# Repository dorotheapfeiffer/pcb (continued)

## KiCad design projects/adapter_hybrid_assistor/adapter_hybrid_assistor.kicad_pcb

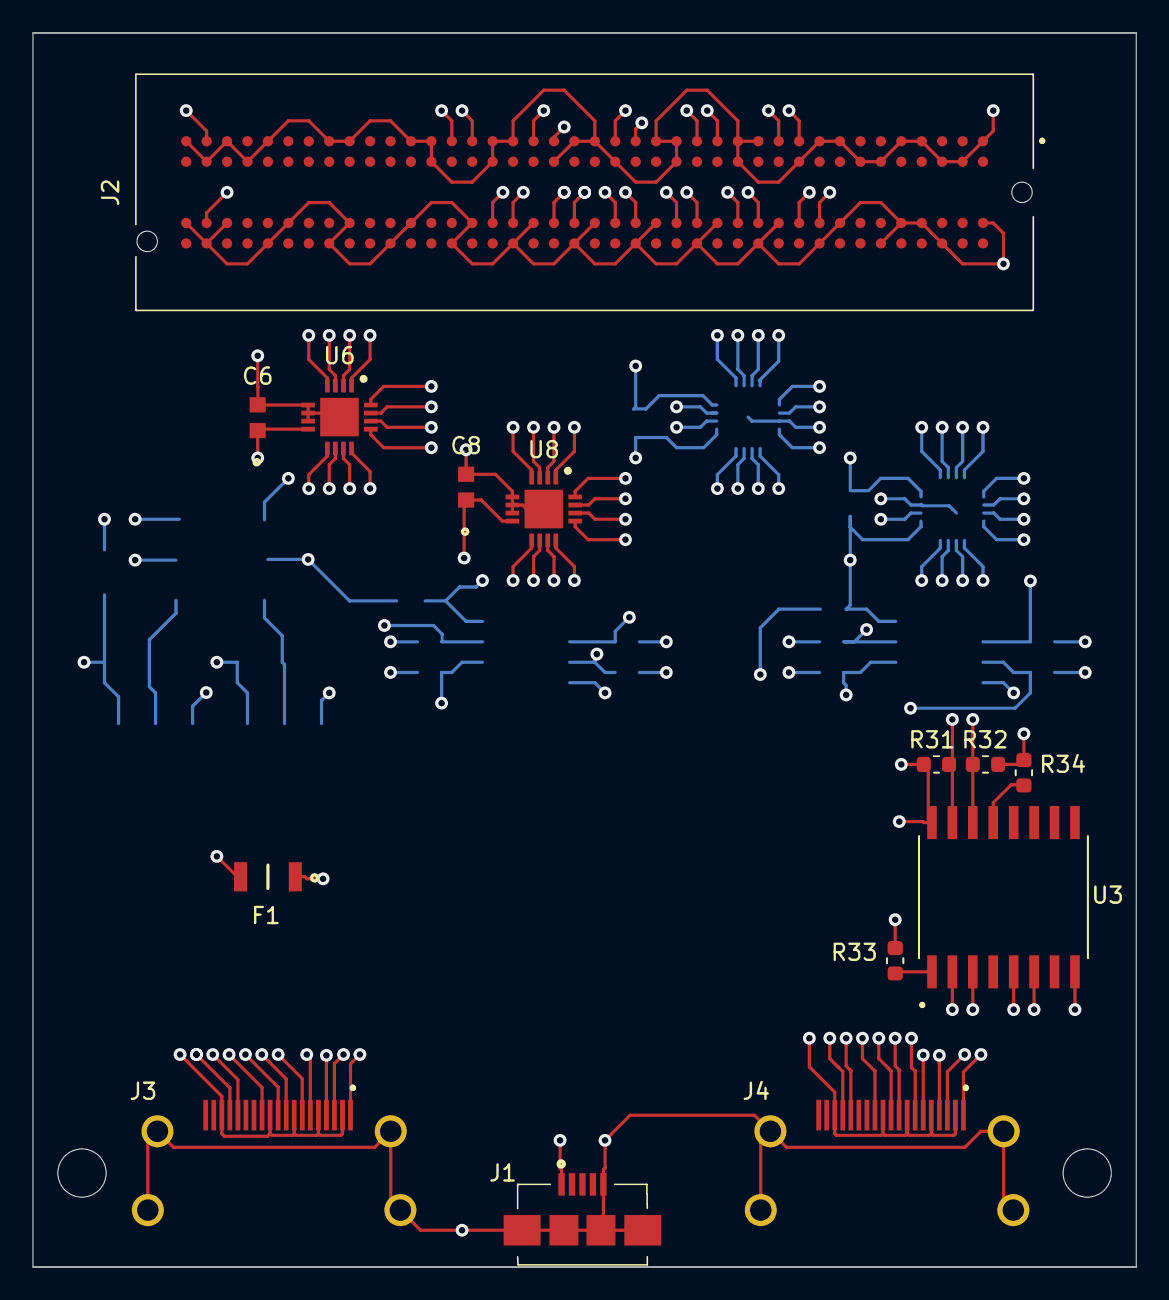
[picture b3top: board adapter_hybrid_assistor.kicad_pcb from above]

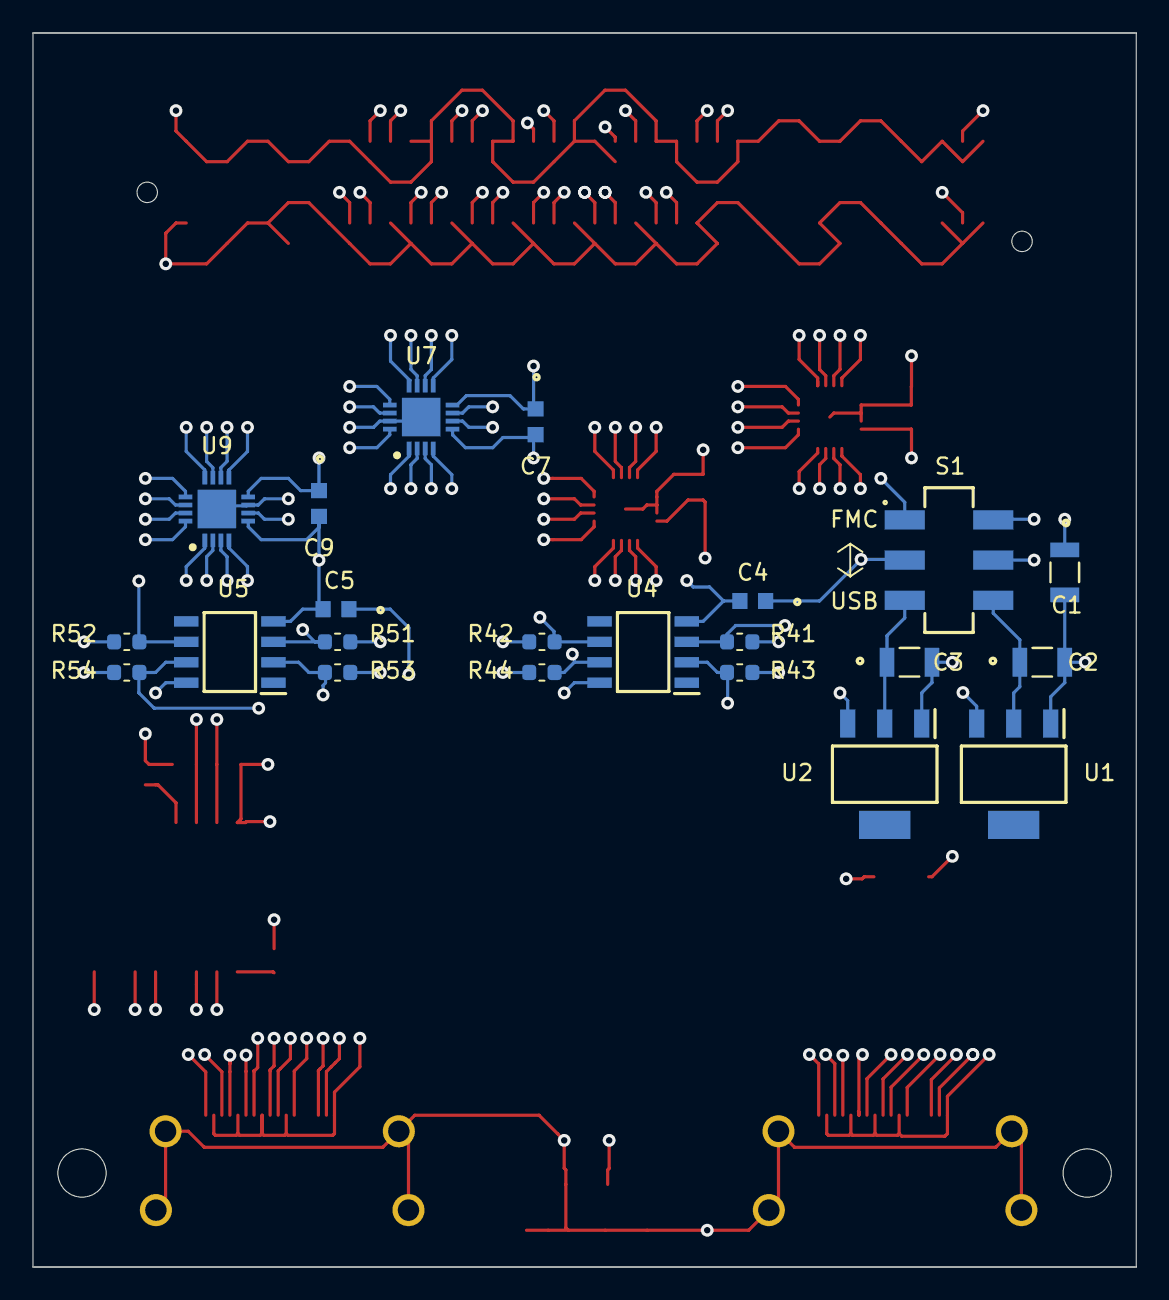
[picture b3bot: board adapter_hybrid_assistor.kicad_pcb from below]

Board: 6 copper layers, 68.6 x 76.7 mm, 36 parts (22 on the bottom side), 55 nets.

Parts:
C1, C2, C3: 10uF; C1206C106K4RACTU
C4, C5, C6, C7, C8, C9: 100nF; C0603C104K4RACTU
F1: 1206L050YR; FUSC3216X75N
J1: 10104110-0001LF; 101041100001LF
J2: ASP-134604-01; ASP13460401
J3, J4: 10029449-001RLF; 10029449001RLF
R31, R32, R33, R41, R42, R51, R52: 4.7k; R_0603_1608Metric
R34: 100k; R_0603_1608Metric
R43, R44, R53, R54: 330; R_0603_1608Metric
S1: JS202011SCQN
U1: TLV1117-33; TLV1117-33IDCYG3
U2: TLV1117-25; TLV1117-25CDCYRG3
U3: PCA9534DW; SOIC127P1030X265-16N
U4, U5: P82B715DR
U6, U7, U8, U9: DS25CP102TSQ; QFN50P400X400X80-17N

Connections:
2.5V: C4.1, C5.1, R43.1, R44.1, R53.1, R54.1, S1.2
2.5V_Supply: C3.1, S1.3, U2.2
2.5V_VADJ_FMC: J2.G39, S1.1
3.3V: C6.1, C7.1, C8.1, C9.1, R31.1, R32.1, R33.1, R34.1, R41.1, R42.1, R51.1, R52.1, S1.5, U3.16, U4.8, U5.8, U6.8, U6.13, U6.14, U6.16, U7.8, U7.13, U7.14, U7.16, U8.8, U8.13, U8.14, U8.16, U9.8, U9.13, U9.14, U9.16
3.3V_FMC: J2.C39, S1.4
3.3V_Supply: C2.1, S1.6, U1.2
/5.0V: C1.1, F1.2, U1.3, U2.3
/5.0V_USB: F1.1, J1.1
/A0: R33.2, U3.1
/D_OUT_M1_1N: J2.C11, U7.11
/D_OUT_M1_1P: J2.C10, U7.12
/D_OUT_M2_1N: J2.C15, U7.9
/D_OUT_M2_1P: J2.C14, U7.10
/~INT: R34.2, U3.13
BCLK_1N: J2.C23, U6.4
BCLK_1P: J2.C22, U6.3
BCLK_2N: J2.G19, U8.4
BCLK_2P: J2.G18, U8.3
D_OUT_M1_2N: J2.G10, U9.11
D_OUT_M1_2P: J2.G9, U9.12
D_OUT_M2_2N: J2.G13, U9.9
D_OUT_M2_2P: J2.G12, U9.10
EQ: U3.6, U7.6, U9.6
GNDREF: C1.2, C2.2, C3.2, C4.2, C5.2, C6.2, C7.2, C8.2, C9.2, J1.5, J1.MP1, J1.MP2, J1.MP3, J1.MP4, J2.C1, J2.C4, J2.C5, J2.C8, J2.C9, J2.C12, J2.C13, J2.C16, J2.C17, J2.C20, J2.C21, J2.C24, J2.C25, J2.C28, J2.C29, J2.C32, J2.C33, J2.C36, J2.C38, J2.C40, J2.D2, J2.D3, J2.D6, J2.D7, J2.D10, J2.D13, J2.D16, J2.D19, J2.D22, J2.D25, J2.D28, J2.D37, J2.D39, J2.G1, J2.G4, J2.G5, J2.G8, J2.G11, J2.G14, J2.G17, J2.G20, J2.G23, J2.G26, J2.G29, J2.G32, J2.G35, J2.G38, J2.G40, J2.H3, J2.H6, J2.H9, J2.H12, J2.H15, J2.H18, J2.H21, J2.H24, J2.H27, J2.H30, J2.H33, J2.H36, J2.H39, J3.2, J3.5, J3.8, J3.11, J3.17, J3.MH1, J3.MH2, J3.MH3, J3.MH4, J4.2, J4.5, J4.8, J4.11, J4.17, J4.MH1, J4.MH2, J4.MH3, J4.MH4, U1.1, U2.1, U3.2, U3.3, U3.8, U4.4, U5.4, U6.5, U6.6, U6.7, U6.17, U7.5, U7.7, U7.15, U7.17, U8.5, U8.6, U8.7, U8.17, U9.5, U9.7, U9.15, U9.17
H_BCLK_1N: J3.12, U6.9
H_BCLK_1P: J3.10, U6.10
H_BCLK_2N: J4.12, U8.9
H_BCLK_2P: J4.10, U8.10
H_DOUT_M1_1N: J3.3, U7.2
H_DOUT_M1_1P: J3.1, U7.1
H_DOUT_M1_2N: J4.3, U9.2
H_DOUT_M1_2P: J4.1, U9.1
H_DOUT_M2_1N: J3.6, U7.4
H_DOUT_M2_1P: J3.4, U7.3
H_DOUT_M2_2N: J4.6, U9.4
H_DOUT_M2_2P: J4.4, U9.3
H_SCL0B_1: J3.15, R44.2, U4.7
H_SCL0B_2: J4.15, R54.2, U5.7
H_SDA0B_1: J3.16, R43.2, U4.2
H_SDA0B_2: J4.16, R53.2, U5.2
H_TRG_1N: J3.9, U6.11
H_TRG_1P: J3.7, U6.12
H_TRG_2N: J4.9, U8.11
H_TRG_2P: J4.7, U8.12
PE: U3.5, U6.15, U8.15
SCL0B_1: J2.C26, R42.2, U4.6
SCL0B_2: J2.G21, R52.2, U5.6
SCL1B: J2.G24, R32.2, U3.14
SDA0B_1: J2.C27, R41.2, U4.3
SDA0B_2: J2.G22, R51.2, U5.3
SDA1B: J2.G25, R31.2, U3.15
TRG_1N: J2.C19, U6.2
TRG_1P: J2.C18, U6.1
TRG_2N: J2.G16, U8.2
TRG_2P: J2.G15, U8.1

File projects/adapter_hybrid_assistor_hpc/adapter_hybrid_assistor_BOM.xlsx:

Id | Designator | Designation | Package | Quantity | Value | Place_YES/NO | Provided_by_customer_YES/NO | Supplier | Supplier ref | Manufacturer | Montage
2 | J1 | ASP13460401 |  | 1 |  | YES | NO | Mouser | 200-ASP-134604-01 | Samtec | Solder Balls
6 | U7,U6,U9,U8 | DS25CP102TSQ | WQFN-16 | 4 |  | YES | NO | Mouser | 926-DS25CP102TSQNOPB | Texas Instruments | SMD/SMT
7 | U5,U4 | P82B715DR | SOIC-8 | 2 |  | YES | NO | Mouser | 595-P82B715DR | Texas Instruments | SMD/SMT
11 | J2,J3 | 10029449001RLF |  | 2 |  | YES | NO | Mouser | 649-10029449-001RLF | Amphenol FCI | SMD/SMT
12 | R41,R42,R51,R52 | ERA-3ARB472V | 0603 (1608 metric) | 4 | 4.7k | YES | NO | Mouser | 667-ERA-3ARB472V | Panasonic | SMD/SMT
14 | R43,R44,R53,R54 | ERA-3AED331V | 0603 (1608 metric) | 4 | 330 | YES | NO | Mouser | 667-ERA-3AED331V | Panasonic | SMD/SMT
15 | C4,C5,C6,C7,C8,C9 | C0603C104K4RACTU | 0603 (1608 metric) | 6 | 100nF | YES | NO | Mouser | 80-C0603C104K4R | KEMET | SMD/SMT
 |  |  |  | 23

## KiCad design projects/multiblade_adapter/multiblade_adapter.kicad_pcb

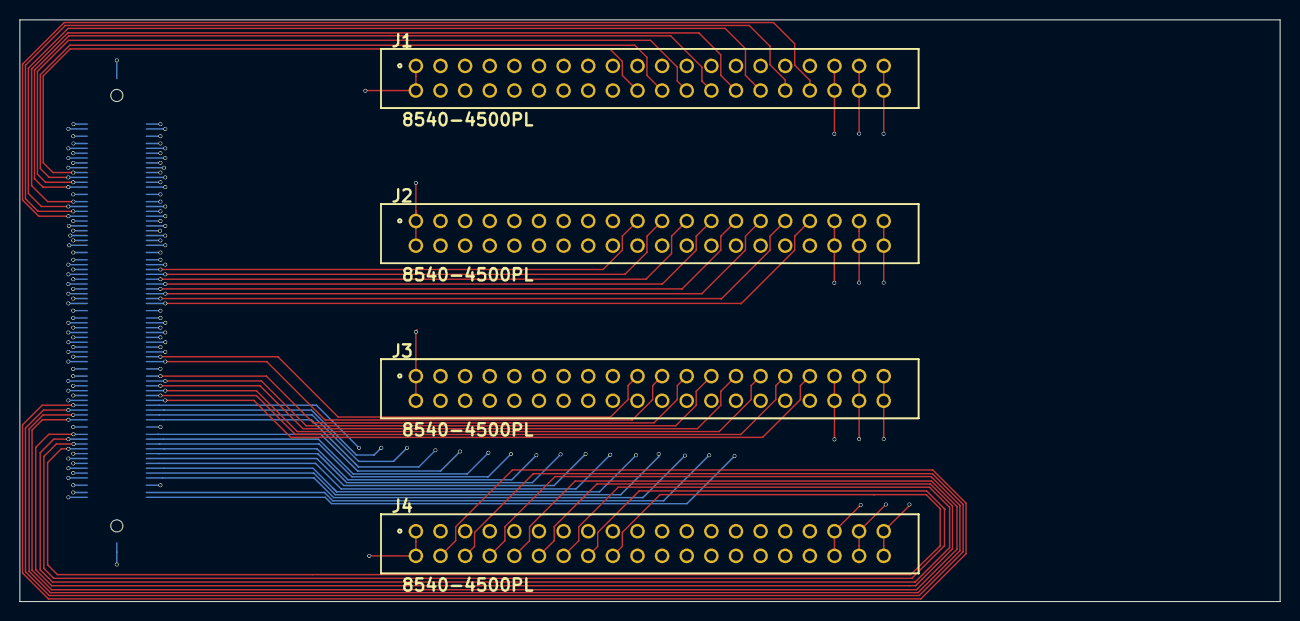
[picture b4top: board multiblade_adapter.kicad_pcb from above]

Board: 6 copper layers, 130.0 x 60.0 mm, 5 parts (1 on the bottom side), 129 nets.

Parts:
J1, J2, J3, J4: 8540-4500PL; 3M-8540-4500PL
J5: FX10A-140S14-SV

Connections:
GND: J1.1, J1.2, J1.35, J1.36, J1.37, J1.38, J1.39, J1.40, J2.1, J2.2, J2.35, J2.36, J2.37, J2.38, J2.39, J2.40, J3.1, J3.2, J3.35, J3.36, J3.37, J3.38, J3.39, J3.40, J4.1, J4.2, J4.35, J4.36, J4.37, J4.38, J4.39, J4.40, J5.141, J5.142, J5.143, J5.144, J5.145, J5.146, J5.147, J5.148, J5.149, J5.150, J5.151, J5.152, J5.153, J5.154, J5.155, J5.156
ch1_1: J1.3, J5.8
ch1_2: J2.3, J5.40
ch1_3: J3.3, J5.72
ch1_4: J4.3, J5.104
ch2_1: J1.4, J5.7
ch2_2: J2.4, J5.39
ch2_3: J3.4, J5.71
ch2_4: J4.4, J5.103
ch3_1: J1.5, J5.10
ch3_2: J2.5, J5.42
ch3_3: J3.5, J5.74
ch3_4: J4.5, J5.106
ch4_1: J1.6, J5.9
ch4_2: J2.6, J5.41
ch4_3: J3.6, J5.73
ch4_4: J4.6, J5.105
ch5_1: J1.7, J5.12
ch5_2: J2.7, J5.44
ch5_3: J3.7, J5.76
ch5_4: J4.7, J5.108
ch6_1: J1.8, J5.11
ch6_2: J2.8, J5.43
ch6_3: J3.8, J5.75
ch6_4: J4.8, J5.107
ch7_1: J1.9, J5.14
ch7_2: J2.9, J5.46
ch7_3: J3.9, J5.78
ch7_4: J4.9, J5.110
ch8_1: J1.10, J5.13
ch8_2: J2.10, J5.45
ch8_3: J3.10, J5.77
ch8_4: J4.10, J5.109
ch9_1: J1.11, J5.16
ch9_2: J2.11, J5.48
ch9_3: J3.11, J5.80
ch9_4: J4.11, J5.112
ch10_1: J1.12, J5.15
ch10_2: J2.12, J5.47
ch10_3: J3.12, J5.79
ch10_4: J4.12, J5.111
ch11_1: J1.13, J5.18
ch11_2: J2.13, J5.50
ch11_3: J3.13, J5.82
ch11_4: J4.13, J5.114
ch12_1: J1.14, J5.17
ch12_2: J2.14, J5.49
ch12_3: J3.14, J5.81
ch12_4: J4.14, J5.113
ch13_1: J1.15, J5.20
ch13_2: J2.15, J5.52
ch13_3: J3.15, J5.84
ch13_4: J4.15, J5.116
ch14_1: J1.16, J5.19
ch14_2: J2.16, J5.51
ch14_3: J3.16, J5.83
ch14_4: J4.16, J5.115
ch15_1: J1.17, J5.22
ch15_2: J2.17, J5.54
ch15_3: J3.17, J5.86
ch15_4: J4.17, J5.118
ch16_1: J1.18, J5.21
ch16_2: J2.18, J5.53
ch16_3: J3.18, J5.85
ch16_4: J4.18, J5.117
ch17_1: J1.19, J5.24
ch17_2: J2.19, J5.56
ch17_3: J3.19, J5.88
ch17_4: J4.19, J5.120
ch18_1: J1.20, J5.23
ch18_2: J2.20, J5.55
ch18_3: J3.20, J5.87
ch18_4: J4.20, J5.119
ch19_1: J1.21, J5.26
ch19_2: J2.21, J5.58
ch19_3: J3.21, J5.90
ch19_4: J4.21, J5.122
ch20_1: J1.22, J5.25
ch20_2: J2.22, J5.57
ch20_3: J3.22, J5.89
ch20_4: J4.22, J5.121
ch21_1: J1.23, J5.28
ch21_2: J2.23, J5.60
ch21_3: J3.23, J5.92
ch21_4: J4.23, J5.124
ch22_1: J1.24, J5.27
ch22_2: J2.24, J5.59
ch22_3: J3.24, J5.91
ch22_4: J4.24, J5.123
ch23_1: J1.25, J5.30
ch23_2: J2.25, J5.62
ch23_3: J3.25, J5.94
ch23_4: J4.25, J5.126
ch24_1: J1.26, J5.29
ch24_2: J2.26, J5.61
ch24_3: J3.26, J5.93
ch24_4: J4.26, J5.125
ch25_1: J1.27, J5.32
ch25_2: J2.27, J5.64
ch25_3: J3.27, J5.96
ch25_4: J4.27, J5.128
ch26_1: J1.28, J5.31
ch26_2: J2.28, J5.63
ch26_3: J3.28, J5.95
ch26_4: J4.28, J5.127
ch27_1: J1.29, J5.34
ch27_2: J2.29, J5.66
ch27_3: J3.29, J5.98
ch27_4: J4.29, J5.130
ch28_1: J1.30, J5.33
ch28_2: J2.30, J5.65
ch28_3: J3.30, J5.97
ch28_4: J4.30, J5.129
ch29_1: J1.31, J5.36
ch29_2: J2.31, J5.68
ch29_3: J3.31, J5.100
ch29_4: J4.31, J5.132
ch30_1: J1.32, J5.35
ch30_2: J2.32, J5.67
ch30_3: J3.32, J5.99
ch30_4: J4.32, J5.131
ch31_1: J1.33, J5.38
ch31_2: J2.33, J5.70
ch31_3: J3.33, J5.102
ch31_4: J4.33, J5.134
ch32_1: J1.34, J5.37
ch32_2: J2.34, J5.69
ch32_3: J3.34, J5.101
ch32_4: J4.34, J5.133

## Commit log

2020-04-29 Added Hirose connectors for Kikad
2020-04-30 added schematic
2020-04-30 removed zip
2021-09-13 Added HPC hybrid assister adapter
2021-10-11 added components
2022-11-09 added HPC 2HDMI and 3HDMI
